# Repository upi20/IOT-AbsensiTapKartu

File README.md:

# Absensi RFID Terintegrasi

Alat absensi **tap kartu RFID** berbasis ESP32 yang **terhubung langsung ke website**. Kartu ditempel, alat mengirim nomornya ke server lewat WiFi (HTTP/HTTPS), dan hasilnya (MASUK / PULANG / tidak terdaftar) tampil di layar sentuh 3.5", LED RGB, dan bunyi buzzer. Semua data kehadiran tersimpan di website, bukan di alat.

*Open-source RFID attendance terminal (ESP32 + RC522 + 3.5" touch LCD) that talks to any web app through a small HTTP API. Includes firmware, a Laravel reference server, integration examples, perfboard/PCB layouts and a 3D-printed case. Documentation is in Indonesian.*

Repositori ini berisi **semua yang dibutuhkan dari nol sampai alat jadi**: daftar komponen, kabel prototipe, firmware, server + panel admin, contoh integrasi ke aplikasi lain, tata letak PCB, dan casing cetak 3D.

---

## Daftar isi

- [Fitur](#fitur)
- [Status proyek](#status-proyek-baca-dulu)
- [Cara kerja](#cara-kerja)
- [Peta tahapan](#peta-tahapan)
- [Tahap 0 — Siapkan komponen, alat, dan software](#tahap-0--siapkan-komponen-alat-dan-software)
- [Tahap 1 — Prototipe dengan kabel jumper](#tahap-1--prototipe-dengan-kabel-jumper)
- [Tahap 2 — Firmware](#tahap-2--firmware)
- [Tahap 3 — Backend (website)](#tahap-3--backend-website)
- [Tahap 4 — PCB](#tahap-4--pcb)
- [Tahap 5 — Casing cetak 3D](#tahap-5--casing-cetak-3d)
- [Pemecahan masalah](#pemecahan-masalah)
- [Struktur folder](#struktur-folder)
- [Untuk kontributor](#untuk-kontributor)
- [Lisensi](#lisensi)

Dokumen lain: [Panduan pengguna untuk klien](doc/panduan-pengguna.md) · [Panduan integrasi aplikasi](doc/integrasi-aplikasi.md) · [Riwayat perubahan](CHANGELOG.md)

---

## Fitur

**Alat (firmware ESP32)**
- Tap kartu MIFARE 13,56 MHz (RC522), hasil tampil dalam ± 0,4–0,6 detik di jaringan normal.
- Semua pengaturan lewat **layar sentuh**: pilih WiFi, isi password, Base URL server, dan API key. Tidak perlu mengubah kode untuk tiap lokasi.
- **Antrean offline** 200 tap: kalau server tidak bisa dihubungi, tap disimpan dan dikirim ulang otomatis (tanpa catatan ganda berkat `tap_id`).
- Foto pemilik kartu (JPEG kecil), pesan dari server, jam tersinkron.
- **Screensaver pengumuman** (judul, isi, ikon) yang diambil dari website.
- **Layar meredup** saat alat diam; kartu tetap terbaca.
- Menu Pengaturan ber-PIN, kalibrasi layar, tes buzzer & LED, cek kabel RFID, reset pabrik (tekan EN 3 kali).
- Heartbeat tiap menit, sehingga website tahu alat mana yang aktif.
- Tahan menyala lama: **watchdog** (restart sendiri kalau program macet) dan **restart harian terjadwal** saat sepi (jamnya diatur per alat dari website, bawaan 03:00).
- **Mode absen**: otomatis (server menentukan datang/pulang) atau **pilih DATANG / PULANG** lewat dua tombol di layar utama (endpoint `/check-in` & `/check-out`), diatur dari menu alat atau dari website.
- Mudah dirawat dari jauh: **kode error di layar** (contoh `E11` = password WiFi salah), laporan kesehatan dan **ringkasan crash** ke website, dan **update firmware jarak jauh (OTA)** yang kembali sendiri ke versi lama kalau firmware baru gagal.

**Website**
- **API sederhana** (`/ping`, `/tap`, `/heartbeat`, opsional `/announcements`) yang bisa diterapkan di aplikasi apa saja: lihat [doc/spesifikasi-api.md](doc/spesifikasi-api.md).
- **Server acuan Laravel** dengan panel admin: anggota & kartu, kehadiran, kartu belum terdaftar, rekap + CSV, daftar alat (PIN per alat), pengumuman, pengaturan (API key, judul, layar redup).
- **Contoh integrasi** PHP dan Node.js tanpa framework, skrip pemeriksa server, dan koleksi Postman lengkap.

---

## Status proyek (baca dulu)

Supaya tidak ada yang tersesat: bagian di bawah ini dibedakan antara yang **sudah diuji di alat sungguhan** dan yang **baru berupa desain**.

| Bagian | Status |
|---|---|
| Prototipe kabel jumper di expansion board | ✅ Dirakit dan berjalan |
| Firmware v1.3.0 | ✅ Berjalan di alat prototipe (tap, antrean, pengumuman, layar redup) |
| Firmware v1.4.0 (watchdog, restart harian, identitas baru) | ✅ Berjalan di alat (boot, tap, heartbeat, watchdog aktif); ⚠️ restart harian **belum diuji** |
| Firmware v1.5.0 (kode error, ringkasan crash, update jarak jauh) | ✅ Update jarak jauh diuji di alat (unduh ± 15 detik, rollback saat restart di masa percobaan juga terbukti); ⚠️ tiap kode error belum diuji satu per satu |
| Server Laravel + panel admin | ✅ Dipakai di server percobaan; 145 tes otomatis lulus |
| Contoh integrasi PHP/Node + Postman | ✅ Lolos skrip pemeriksa dan 114 pemeriksaan Postman |
| Firmware v1.6.0–1.9.1 (mode absen DATANG/PULANG, menu Update firmware, buzzer langsung ke D17) | ✅ Dikirim ke alat lewat update jarak jauh: otomatis 1.5.0 → 1.6.0 → 1.7.0, manual 1.7.0 → 1.8.0 → 1.9.0 → 1.9.1. ⚠️ Mode Pilih Datang/Pulang **belum diuji dengan tap sungguhan** |
| PCB dot matrix (papan bolong 1 sisi 30 × 50) | ✅ Alat pertama dirakit dengan tata letak ini dan berjalan (layar, sentuh, RFID, WiFi, tap, buzzer). ⚠️ Kabel LED (tahap 16) belum diuji; casing belum disesuaikan |
| PCB cetak (KiCad) | ⚠️ Desain lolos DRC, **belum dipesan dan belum diuji** |
| Casing cetak 3D | ⚠️ Desain lolos cek tabrakan otomatis, **belum dicetak** |

Kalau Anda merakit bagian yang bertanda ⚠️, lakukan cek cetak kertas 1:1 yang dijelaskan di tahap itu, dan laporkan hasilnya lewat *Issues*.

---

## Cara kerja

```mermaid
flowchart LR
  K[Kartu RFID] -->|tap| A["Alat<br/>ESP32 + RC522 + LCD"]
  A -->|"POST /tap (WiFi, HTTPS)"| W["Website<br/>(server acuan Laravel<br/>atau aplikasi Anda)"]
  W -->|"status: MASUK / PULANG / ..."| A
  A -.->|heartbeat tiap 1 menit| W
  W -.->|pengaturan & pengumuman| A
  W --> P[Panel admin / laporan]
```

1. Kartu ditempel. Alat membaca UID kartu dan mengubahnya menjadi **nomor 10 digit**.
2. Alat mengirim `POST {Base URL}/tap` dengan header `X-API-Key` dan `X-Device-ID`.
3. Website memutuskan statusnya (`check_in`, `check_out`, `duplicate`, `unknown`, `rejected`) dan membalas nama, pesan, dan (opsional) URL foto.
4. Alat menampilkan hasil, berbunyi, dan menyalakan LED sesuai status.

Website juga bisa mengirim **pengaturan jarak jauh** (PIN menu, judul layar, layar redup) dan **pengumuman** ke alat. Kontrak lengkapnya ada di [doc/spesifikasi-api.md](doc/spesifikasi-api.md).

---

## Peta tahapan

| Tahap | Hasil | Dokumen utama |
|---|---|---|
| 0. Persiapan | Komponen, alat, software siap | bagian di bawah |
| 1. Prototipe | Rangkaian kabel jumper berjalan | [doc/skema-lengkap.md](doc/skema-lengkap.md), [doc/rakit-lengkap.html](doc/rakit-lengkap.html) |
| 2. Firmware | Alat membaca kartu dan tampil di layar | [firmware/](firmware/) |
| 3. Backend | Website menerima tap, panel admin | [api/README.md](api/README.md), [doc/integrasi-aplikasi.md](doc/integrasi-aplikasi.md), [doc/spesifikasi-api.md](doc/spesifikasi-api.md), [contoh-integrasi/](contoh-integrasi/README.md) |
| 4. PCB | Rangkaian rapi tanpa kabel jumper | [doc/rakit-dotmatrix.html](doc/rakit-dotmatrix.html), [doc/pcb-papan-induk.md](doc/pcb-papan-induk.md) |
| 5. Casing | Alat jadi, siap dipasang di dinding | [doc/casing.md](doc/casing.md) |

> **File `.html`** di folder `doc/` adalah panduan interaktif. GitHub hanya menampilkan kodenya, jadi **unduh repositori lalu buka file itu di browser** (dobel klik).

---

## Tahap 0 — Siapkan komponen, alat, dan software

### Komponen (1 unit)

| Komponen | Keterangan | Catatan |
|---|---|---|
| ESP32 DOIT DevKit V1 **30 pin** | Chip USB CH340, jarak dua deret pin 25,4 mm | Varian 38 pin **tidak** cocok dengan PCB dan casing |
| LCD 3.5" SPI **ILI9488** + touch **XPT2046** | 480 × 320, 14 pin di satu sisi pendek, PCB 98 × 56,34 mm (kompatibel LCDWIKI MSP3520) | Jumper **J1** di belakang LCD harus disolder (lihat Tahap 1) |
| RFID **RC522** | Modul standar 60 × 40 mm, 8 pin, 3,3 V | Header pin lurus |
| LED RGB 5 mm **common cathode** | 4 kaki, kaki terpanjang = katoda (−) | Bukan *common anode* |
| Buzzer **aktif** 3–5 V | 2 kaki, berbunyi sendiri bila diberi tegangan | Bukan buzzer pasif |
| Kartu / gantungan kunci MIFARE 13,56 MHz | Biasanya satu paket dengan RC522 | |
| Kabel USB data + adaptor 5 V | Untuk daya alat | |

**Untuk prototipe (Tahap 1):** expansion board ESP32 30 pin (header G-V-S per pin) dan ± 30 kabel jumper female-female.
**Untuk versi rapi (Tahap 4):** papan dot matrix atau PCB cetak beserta komponen kecilnya (resistor, transistor, dioda, kapasitor, header female). Daftarnya ada di tahap itu.

### Alat

Solder + timah, tang potong, multimeter (mode bunyi dan volt DC), obeng kecil. Untuk Tahap 4: cutter, bor 3 mm, lem. Untuk Tahap 5: baut M3 dan spacer.

### Software

| Software | Untuk | Versi yang dipakai di proyek ini |
|---|---|---|
| [Arduino IDE 2](https://www.arduino.cc/en/software) (atau `arduino-cli`) | Firmware | IDE 2.3.10 / arduino-cli 1.5.1 |
| Paket board **esp32 by Espressif Systems** | Firmware | 3.3.12 |
| PHP 8.3 + Composer + PostgreSQL | Server acuan (Tahap 3) | PHP 8.3, Laravel 13 |
| KiCad 10 (opsional) | Membuka / mengubah PCB cetak | 10.0.6 |
| OpenSCAD versi *snapshot* (opsional) | Membuka / mengubah casing | 2026.09.30 |
| Python 3 + PyMuPDF (opsional) | Membuat ulang templat dot matrix | |

---

## Tahap 1 — Prototipe dengan kabel jumper

Tujuannya membuktikan semua komponen berfungsi sebelum dibuat rapi. **Cabut USB setiap kali memasang atau memindah kabel.**

### 1.1 Aturan daya (penting)

- **Semua komponen memakai 3,3 V.** Jangan ada kabel ke pin 5V.
- Di expansion board, jumper **JUMP** harus di posisi **3.3V** (mengatur semua pin V).
- Pakai satu kabel USB saja, ke port **ESP32** (bukan port expansion).
- ESP32 hanya bisa tersambung ke WiFi **2,4 GHz**.

### 1.2 Solder jumper J1 di LCD

Menurut skema resmi modul LCD: kalau VCC diberi **3,3 V**, jumper **J1 harus disambung** (dijembatani timah). Kalau VCC 5 V, J1 dibiarkan terbuka. Rangkaian ini memakai 3,3 V, jadi:

1. Cari bantalan bertanda **J1** di belakang LCD (dekat regulator U1).
2. Sambungkan kedua bantalannya dengan sedikit timah.
3. Setelah J1 disambung, **VCC LCD tidak boleh lagi diberi 5 V**: chip layar bisa rusak.

### 1.3 Pasang kabel

Ikuti [doc/skema-lengkap.md](doc/skema-lengkap.md) (versi interaktif: [doc/rakit-lengkap.html](doc/rakit-lengkap.html)). Ringkasan pin:

| Bagian | Pin modul → GPIO ESP32 |
|---|---|
| LCD | VCC → 3V3, GND → GND, CS → 5, RESET → 4, DC → **16**, SDI → 23, SCK → 18, **LED → 2**, SDO tidak disambung |
| Touch | T_CLK → 22, T_CS → 15, T_DIN → 21, T_DO → 19, T_IRQ tidak disambung |
| RC522 | SDA → 33, SCK → 14, MOSI → 13, MISO → 35, RST → 32, 3.3V → 3V3, GND → GND, IRQ tidak disambung |
| Buzzer aktif | + → 17, − → GND |
| LED RGB | R → 25, G → 26, B → 27, kaki terpanjang (K) → GND |
| *atau* RTC DS3231 (pengganti LED) | SDA → 25, SCL → 26, VCC → 3V3, GND → GND |

Catatan:
- **DC jangan di GPIO2.** Pin LED LCD (lampu latar) memang di GPIO2; firmware memakainya untuk meredupkan layar. Kalau LED LCD disambung ke 3V3, layar menyala terus tanpa fitur redup.
- Pin **GPIO12 jangan dipakai** (pin boot yang membuat ESP32 gagal menyala).
- Resistor 220–330 Ω di tiap kaki warna LED RGB disarankan. Untuk prototipe boleh tanpa resistor karena firmware membatasi arus pin.
- **RTC DS3231 (opsional, firmware 1.10.0+)** menyimpan jam selama listrik mati, sehingga tap saat alat menyala tanpa internet tetap tercatat dengan jam aslinya. RTC memakai pin LED RGB (25, 26), jadi pilih salah satu: LED **atau** RTC. Firmware mendeteksinya sendiri saat menyala. Pakai modul **DS3231** (mis. ZS-042, 3,3 V), bukan DS1307 (butuh 5 V). Di papan dot matrix: kabel header LED dipakai ulang (R = SDA, G = SCL, K = GND), dan kaki R3 yang tersambung ke D27 dipindah ke 3V3 sehingga B = VCC. Jam internet tetap diutamakan; RTC disetel ulang darinya.

### 1.4 Tes per bagian

Sebelum menjalankan tes, siapkan software di [Tahap 2.1](#21-pasang-software). Sketsa tes ada di [firmware/tes/](firmware/tes/):

| Urutan | Sketsa | Yang dites | Hasil yang benar |
|---|---|---|---|
| 1 | `tes_touch` | Layar + layar sentuh | Muncul kalibrasi 3 titik, lalu mode menggambar: titik muncul tepat di bawah jari/stylus |
| 2 | `tes_miso` | Kabel MOSI dan MISO RC522 tidak bersentuhan | Monitor serial menulis `AMAN` terus-menerus |
| 3 | `tes_rfid` | RC522 menjawab | Baris pertama (susunan kabel yang direncanakan) diakhiri `<== RC522 MENJAWAB` |

Buzzer dan LED dites dari firmware utama (menu **Tes buzzer & LED**), setelah Tahap 2.

---

## Tahap 2 — Firmware

Kode ada di [firmware/absensi/](firmware/absensi/). Bahasa komentar: Indonesia.

### 2.1 Pasang software

1. Pasang **Arduino IDE 2**.
2. **Tools → Board → Boards Manager**, cari `esp32`, pasang **esp32 by Espressif Systems** (dipakai: 3.3.12). Kalau tidak muncul, tambahkan URL `https://espressif.github.io/arduino-esp32/package_esp32_index.json` di **Settings → Additional boards manager URLs**.
3. **Tools → Manage Libraries**, pasang:

   | Library | Versi dipakai | Untuk |
   |---|---|---|
   | TFT_eSPI (Bodmer) | 2.5.43 | Layar |
   | RFID_MFRC522v2 | 2.0.6 | RC522 |
   | ArduinoJson (Benoit Blanchon) | 7.4.3 | JSON |
   | TJpg_Decoder (Bodmer) | 1.1.0 | Foto |
   | XPT2046_Touchscreen (Paul Stoffregen) | 1.4 | Hanya untuk sketsa `tes_touch` |

   Pengaturan pin layar ada di `tft_setup.h` di folder sketsa dan dibaca otomatis oleh TFT_eSPI. **File library tidak perlu diubah.**
4. **Mac Apple Silicon:** pasang Rosetta 2 (alat `ctags` di paket Arduino masih x86):
   ```bash
   softwareupdate --install-rosetta --agree-to-license
   ```
5. **Windows:** pasang driver **CH340** kalau port COM tidak muncul.

### 2.2 Atur ID alat

Buka [firmware/absensi/config.h](firmware/absensi/config.h), ubah `ID_ALAT` (bawaan `"ABS-001"`). **Setiap alat harus punya ID berbeda**; ID ini dikirim sebagai `X-Device-ID` dan tidak terhapus saat reset pabrik. Isi `""` supaya dibuat otomatis dari alamat MAC (contoh `ABS-79438C`).

Sejak v1.5.0, ID yang dipakai juga disimpan di memori alat. Upload lewat USB memakai `ID_ALAT` di `config.h`. Update jarak jauh (2.7) tidak memakai `ID_ALAT`, tapi ID yang tersimpan di alat, jadi satu file firmware aman dikirim ke semua alat.

Pengaturan lain di file yang sama (biasanya tidak perlu diubah): PIN bawaan `2026`, interval heartbeat 60 detik, batas antrean 200, batas waktu tap 3 detik, layar redup 60 detik ke 20 %.

### 2.3 Upload

**Lewat Arduino IDE (semua sistem operasi):**
1. Buka `firmware/absensi/absensi.ino`.
2. Board: **ESP32 Dev Module** (bukan "DOIT ESP32 DEVKIT V1", karena yang itu tidak punya menu partisi).
3. **Partition Scheme: Minimal SPIFFS (1.9MB APP with OTA/128KB SPIFFS)**. Wajib: firmware ± 1,35 MB tidak muat di partisi bawaan, dan skema ini punya 2 slot untuk update jarak jauh.
4. Upload Speed: **460800** (Mac/Linux). Kalau upload gagal atau di Windows, pakai **115200**.
5. Pilih port, klik Upload. Kalau tertahan di `Connecting....`, tahan tombol **BOOT** sampai persentase muncul.

**Lewat skrip (Mac/Linux, butuh `arduino-cli`):** dari folder `firmware/`:
```bash
./upload.sh -m              # compile + upload firmware utama, lalu buka monitor serial
./upload.sh -c              # compile saja (cek tanpa alat)
./upload.sh -b              # buat file untuk update jarak jauh (lihat 2.7)
./upload.sh tes_rfid -m     # upload sketsa tes
./monitor.sh                # monitor serial 115200 baud, keluar: Ctrl+C
PORT=/dev/ttyUSB0 ./upload.sh    # pilih port sendiri
```
Skrip memakai partisi Minimal SPIFFS dan kecepatan 460800 secara otomatis. `arduino-cli` dicari di `PATH`, lalu di dalam Arduino IDE (macOS). Lokasi lain: `ARDUINO_CLI=/path/arduino-cli ./upload.sh`.

> **Alat dengan firmware ≤ 1.4.0** (partisi lama Huge APP) harus di-upload **sekali lewat USB** ke v1.5.0, karena partisinya berubah. Pengaturan (WiFi, Base URL, API key, PIN, kalibrasi) tetap, tapi antrean tap dan pengumuman yang tersimpan terhapus. Kirim dulu antrean yang tersisa (tunggu sampai Info alat → Antrean = 0). Setelah itu, update berikutnya bisa lewat jarak jauh.

### 2.4 Siapkan server sementara (kalau website belum ada)

Saat pertama menyala, alat meminta **Base URL** dan **API key**. Kalau server Tahap 3 belum siap, jalankan contoh server PHP di laptop (satu WiFi dengan alat):

```bash
cd contoh-integrasi/php
php -S 0.0.0.0:8080 index.php
```

Base URL-nya `http://<IP-laptop>:8080`, API key `ganti-dengan-kunci-anda`. Kartu contoh yang terdaftar: `0218893066` dan `0012345678` (`0055555555` sengaja nonaktif). Kartu Anda sendiri akan tampil "tidak terdaftar" sampai nomornya ditambahkan ke data contoh. Ini cukup untuk membuktikan alat bekerja. Rinciannya: [contoh-integrasi/README.md](contoh-integrasi/README.md).

### 2.5 Pertama kali menyala

Alat baru (atau setelah reset pabrik) menjalankan urutan ini:
1. **Kalibrasi layar sentuh** 3 titik (hanya kalau belum pernah).
2. **Panduan 4 langkah:**
   1. **WiFi**: pilih dari hasil pindai (atau "Ketik manual"), isi password.
   2. **Base URL**: sudah terisi `https://`. Lengkapi, contoh `https://absensi.example.com/api/absensi` atau `http://192.168.1.10:8080`. Tanpa `/` di akhir.
   3. **API key**: sama persis dengan di server.
   4. **Tes koneksi**, lalu **Simpan**.
3. Layar utama tampil. Tempel kartu.

Monitor serial (115200 baud) menampilkan catatan seperti `RFID: RC522 terdeteksi`, `HTTP POST /tap -> 200`, dan `Tap: 245 ms`.

### 2.6 Menu dan fitur alat

| Fitur | Cara |
|---|---|
| Menu Pengaturan | Ikon gir di layar utama, PIN bawaan **2026** (5 kali salah = terkunci 60 detik). Menu tertutup sendiri setelah 60 detik tanpa sentuhan |
| Isi menu | WiFi, Server, Tes koneksi, Info alat, Ganti PIN, Kalibrasi layar, Tes buzzer & LED (alat dengan RTC: Tes buzzer), Tes screensaver, Cek kabel RFID, Mode absen, Update firmware, Reset pabrik |
| Mode absen | Menu **Mode absen**: **Otomatis** (semua tap ke `/tap`, server menentukan datang/pulang) atau **Pilih Datang / Pulang**: layar utama menampilkan tombol **DATANG** dan **PULANG**. Petugas memilih sekali, lalu semua tap dikirim ke `/check-in` atau `/check-out` sampai diganti. Pilihan dikosongkan otomatis saat tanggal berganti; tap sebelum memilih tidak dikirim. Bisa juga diatur per alat dari website (`config.tap_mode`) |
| Kalibrasi ulang layar | Menu **Kalibrasi layar**, atau tekan **EN** lalu tekan **BOOT** saat muncul "Tekan BOOT sekarang" (jeda 1 detik) |
| Reset pabrik | Tekan **EN 3 kali berturut-turut** (masing-masing sebelum alat menyala 5 detik), lalu pilih "Ya, reset"; atau lewat menu. Menghapus WiFi, URL, API key, PIN, judul, kalibrasi, antrean, pengumuman. **ID alat tidak terhapus** |
| Layar redup | Setelah diam 60 detik, layar meredup ke 20 %. Kartu tetap diproses. Sentuhan pertama hanya menyalakan layar. Angka bisa diubah dari website (`dim_after`, `dim_level`) |
| Antrean offline | Server tidak terjangkau → tap disimpan (maks. 200) dan dikirim ulang saat alat diam |
| Restart harian | Sekali sehari pada jam yang diatur per alat di website (bawaan **03:00**, jam alat), hanya saat alat diam. Antrean tap tetap tersimpan. Kosongkan jamnya di website untuk mematikan |
| Watchdog | Kalau program macet lebih dari 60 detik, alat restart sendiri. Alasan restart terakhir terlihat di **Info alat → Restart** dan dikirim ke website |
| Kode error | Masalah tampil di baris bawah layar utama dengan kode, contoh **E11 Password WiFi salah**. Daftar lengkap di 2.8. Kode yang sedang aktif juga ada di **Info alat → Error** |
| Laporan ke website | Tiap menit: sinyal, RAM, status RFID, antrean, kode error, alasan restart, dan ringkasan crash terakhir. Website menandai alat yang perlu diperhatikan |
| Update jarak jauh | Firmware baru diunggah di website, lalu alat memasangnya sendiri saat diam, **atau langsung lewat menu Update firmware** (lihat 2.7) |
| Pengaturan dari website | PIN menu (per alat), jam restart (per alat), judul layar, layar redup, pengumuman, update firmware (per alat) |

### 2.7 Update firmware jarak jauh (OTA)

Dipakai untuk memperbarui alat yang sudah terpasang di lokasi **tanpa kabel USB**: file firmware diunggah ke website, lalu alat mengunduh dan memasangnya sendiri.

**Syarat (cukup dicek sekali):**
- Alat sudah ber-firmware **1.5.0 atau lebih baru**. Alat dengan firmware lama harus di-upload lewat USB dulu (lihat catatan di 2.3), karena partisinya berbeda.
- Website mendukung update firmware. Server acuan Laravel (Tahap 3.A) sudah punya menu **Firmware**. Aplikasi sendiri: lihat [doc/spesifikasi-api.md](doc/spesifikasi-api.md) bagian 6.1.

#### Langkah 1 — Naikkan nomor versi

Buka [firmware/absensi/config.h](firmware/absensi/config.h) dan ubah `VERSI_FIRMWARE`, contoh `"1.5.0"` → `"1.5.1"`.

Wajib: alat **mengabaikan** update yang versinya sama dengan versi yang sedang terpasang, dan website menolak file yang di dalamnya tidak ada nomor versi yang Anda isi.

#### Langkah 2 — Build file `.bin`

File untuk OTA **bukan** hasil upload biasa. ID alat tidak boleh ikut tertanam, supaya satu file bisa dikirim ke semua alat dan tiap alat tetap memakai ID-nya sendiri. Pilih salah satu cara:

**Cara A — skrip (Mac/Linux, disarankan).** Dari folder `firmware/`, tanpa alat tersambung:
```bash
./upload.sh -b
```
Hasilnya di folder `firmware/build/`:

| File | Untuk apa |
|---|---|
| `absensi-1.5.1.bin` | **Diunggah ke website** (Langkah 3) |
| `absensi-1.5.1.elf` | **Simpan baik-baik** (jangan diunggah). Hanya file ini yang bisa menerjemahkan laporan crash dari versi 1.5.1 (lihat 2.8) |
| `absensi/` | File sementara hasil compile, abaikan |

**Cara B — Arduino IDE (semua sistem operasi).**
1. Di `config.h`, hapus `//` di depan baris `// #define OTA_BUILD`, sehingga menjadi `#define OTA_BUILD`.
2. Board dan Partition Scheme sama seperti 2.3 (**ESP32 Dev Module**, **Minimal SPIFFS (1.9MB APP with OTA/128KB SPIFFS)**).
3. Menu **Sketch → Export Compiled Binary**. Tunggu sampai selesai.
4. Buka folder `firmware/absensi/build/esp32.esp32.esp32/`. Yang diunggah ke website adalah **`absensi.ino.bin`**. Jangan pakai `absensi.ino.merged.bin`, `absensi.ino.bootloader.bin`, atau `absensi.ino.partitions.bin`. Simpan juga `absensi.ino.elf`, beri nama sesuai versinya.
5. **Kembalikan `//` di depan `#define OTA_BUILD`.** Kalau lupa, upload lewat USB ke alat baru tidak memakai `ID_ALAT`, tapi ID dari MAC (contoh `ABS-79438C`).

#### Langkah 3 — Unggah dan pilih alat (server acuan)

1. Panel admin → **Firmware** → **Unggah firmware**. Isi **Versi** sama persis dengan `VERSI_FIRMWARE` (contoh `1.5.1`), pilih file `.bin`, lalu klik **Unggah**.
2. Panel admin → **Alat** → di kartu alat yang akan diperbarui, pilih **Update firmware ke: 1.5.1**, lalu simpan. Status alat menjadi **"Menunggu alat mengunduh"**.
3. Untuk semua alat sekaligus, pakai tombol **Terapkan ke semua alat** di halaman Firmware. **Cobakan dulu ke satu alat** sampai statusnya "Sudah terpasang", baru ke semua.

#### Langkah 4 — Tunggu alat memasang sendiri

1. Alat menerima tawaran update lewat heartbeat (paling lama 1 menit).
2. Update baru mulai saat **tidak ada kartu atau sentuhan selama 1 menit**, supaya orang yang sedang absen tidak terganggu.
3. Layar menampilkan **"Memperbarui firmware v1.5.0 → v1.5.1"**, bilah kemajuan, dan **"Jangan cabut listrik alat"**. Unduhan memakan waktu ± 15–60 detik, tergantung internet.
4. Alat mengecek isi file (MD5), menampilkan "Firmware terpasang", lalu restart dengan versi baru.
5. Di halaman Alat, status menjadi **"Sudah terpasang"**, dan riwayat kejadian mencatat `Firmware 1.5.0 -> 1.5.1`.

**Atau pasang sekarang juga (manual, firmware 1.7.0 ke atas):** di alat buka **Pengaturan → Update firmware**. Alat langsung bertanya ke server. Kalau muncul **"Tersedia v…"**, tekan **Pasang sekarang** → **Pasang**. Cara ini tidak menunggu alat diam dan tidak menunggu jeda 30 menit setelah gagal, dan alasan kegagalan tampil di layar. Server hanya menawarkan versi yang **sudah dijadwalkan untuk alat itu** (Langkah 3). Kalau belum dijadwalkan, menu menjawab "Sudah versi terbaru".

Selama update, buzzer diam, LED menyala biru, dan tampilan lain (jam, sinyal) berhenti sebentar: semua kemampuan alat dipakai untuk mengunduh. Itu wajar selama bilah kemajuan bergerak.

#### Kalau ada yang salah

| Yang terjadi | Artinya / yang dilakukan |
|---|---|
| Server sudah menawarkan update tapi alat tidak kunjung memasang | Alat sedang dipakai, menu Pengaturan sedang terbuka, atau percobaan pertama gagal tersambung (alat lalu menunggu 30 menit). Pakai **menu Update firmware** untuk memasang langsung dan melihat alasannya |
| Lama di "Menunggu alat mengunduh" | Alat offline, sedang dipakai terus, atau firmware alat masih < 1.5.0. Cek status Online dan versi firmware alat |
| Layar "Update firmware gagal" | Unduhan putus atau file rusak. Alat tetap memakai versi lama dan **mencoba lagi 30 menit kemudian**. Alasannya terlihat di Info alat → Firmware |
| Riwayat: "Firmware 1.5.1 -> 1.5.0" tanpa status gagal | Listrik padam atau tombol EN ditekan di menit pertama setelah update, jadi alat kembali ke versi lama untuk berjaga-jaga. Bukan salah firmware: alat **mengulang update sendiri** (paling banyak 3 kali) |
| Status "Gagal, kembali ke 1.5.0" | Firmware baru crash, macet (watchdog), atau listrik drop (brownout) sebelum dinyatakan sehat (5 menit, atau 1 menit setelah server tersambung), jadi alat **kembali sendiri ke versi lama**. Versi itu tidak dicoba lagi. Perbaiki kodenya (lihat laporan crash di riwayat kejadian), naikkan versi (1.5.2), lalu unggah ulang |
| Website menolak file | Versi yang diisi tidak ditemukan di dalam file (lupa Langkah 1, atau salah ketik), file bukan `absensi.ino.bin`, atau ukuran lebih dari 1,9 MB |

Jangan cabut listrik selama layar "Memperbarui firmware" dan di menit pertama setelah alat restart. Kalaupun terjadi, alat tidak rusak: saat mengunduh, firmware baru ditulis ke slot cadangan dan baru dipakai setelah selesai dicek; sesudah restart, alat kembali ke versi lama lalu mengulang update.

Catatan keamanan: alat memakai HTTPS tanpa pemeriksaan sertifikat (sama seperti request lain). Orang yang bisa menyadap jaringan alat secara teori bisa mengirim firmware palsu. Karena itu, update hanya dikirim ke alat yang dipilih di website.

### 2.8 Kode error di layar

Konsumen cukup menyebutkan kode yang tampil di baris bawah layar (atau di **Info alat → Error**).

| Kode | Arti | Yang dicek |
|---|---|---|
| E10 | WiFi tidak ditemukan | Router menyala? Nama WiFi benar? WiFi harus **2,4 GHz**. Alat terlalu jauh dari router? |
| E11 | Password WiFi salah | Ganti password di Pengaturan → WiFi (password router mungkin baru diganti) |
| E12 | WiFi gagal tersambung | Router penuh atau menolak perangkat baru (filter MAC). Restart router |
| E13 | WiFi tidak memberi alamat IP | DHCP router mati atau alamat habis. Restart router |
| E20 | Server tidak bisa dihubungi | Internet lokasi putus, atau Base URL salah alamat. Buka website dari HP di WiFi yang sama |
| E21 | API key salah | Samakan API key di alat (Pengaturan → Server) dengan di website |
| E22 | Alat ditolak server | Alat dinonaktifkan / belum diizinkan di website |
| E23 | Alamat API salah | Base URL keliru (harus diakhiri jalur API, tanpa `/` di akhir), atau `http` vs `https` |
| E24 | Server error / sibuk | Masalah di website (HTTP 5xx / 429). Tap tetap disimpan di antrean |
| E25 | Balasan server tidak valid | Base URL mengarah ke halaman biasa, bukan API |
| E26 | Server terlalu lama menjawab | Internet lambat atau server berat |
| E30 | Pembaca RFID tidak terdeteksi | Kabel RC522 longgar. Menu → Cek kabel RFID |
| E31 | Jam belum sinkron | Server tidak mengirim `server_time` dan NTP diblokir jaringan, atau alat menyala tanpa internet dan tidak punya RTC (atau baterai RTC habis) |

**Membaca laporan crash.** Kalau alat pernah crash, halaman Alat di website menampilkan alamat seperti `0x400d4634 0x400880ed` beserta id build. Terjemahkan alamat itu dengan file `.elf` dari versi yang sama:

```bash
~/Library/Arduino15/packages/esp32/tools/esp-x32/*/bin/xtensa-esp32-elf-addr2line -pfiaC \
  -e firmware/build/absensi-1.5.0.elf 0x400d4634 0x400880ed
```
Hasilnya berupa nama fungsi dan baris kode penyebab crash. Linux: ganti `~/Library/Arduino15` dengan `~/.arduino15`.

---

## Tahap 3 — Backend (website)

Pilih salah satu (boleh keduanya):

### 3.A Pakai server acuan Laravel (paling cepat)

Server lengkap dengan panel admin ada di [api/](api/README.md). Ringkasnya:

```bash
cd api
composer install
cp .env.example .env          # isi DB_* (PostgreSQL) dan APP_URL
php artisan key:generate
php artisan migrate           # membuat akun "admin" (tanpa password) dan API key acak
php artisan absensi:admin-password admin
php artisan storage:link
./serve.sh                    # http://127.0.0.1:8133
```

Kebutuhan: PHP ^8.3 (ekstensi pdo_pgsql, mbstring, fileinfo; gd untuk foto), Composer, **PostgreSQL** (SQLite/MySQL tidak didukung). Tidak perlu Node/npm.

Di panel admin (`/admin`):
1. **Pengaturan**: salin **Base URL** (`<APP_URL>/api/absensi`) dan **API key**, isikan di alat.
2. Tempel kartu di alat. Kartu baru muncul di **Kartu belum terdaftar** → klik **Daftarkan** → isi nama → simpan.
3. Tempel lagi: alat menampilkan **MASUK** (tap pertama hari itu). Tap lagi dalam 60 detik = **sudah tercatat**; tap setelahnya = **PULANG**.

Langkah lengkap, opsi, dan perintah artisan: [api/README.md](api/README.md).

### 3.B Integrasikan ke aplikasi Anda sendiri

Alat tidak terikat ke Laravel. Aplikasi apa pun (PHP, Node, Python, Go, ...) bisa memakainya.

1. **Mulai dari [doc/integrasi-aplikasi.md](doc/integrasi-aplikasi.md)**: gambaran besar, **6 fitur wajib** (Kartu belum terdaftar, Rekap, Alat, Firmware, Pengumuman, Pengaturan), data yang perlu disimpan, urutan kerja, dan checklist siap pakai.
2. Kontrak teknis alat ↔ aplikasi: [doc/spesifikasi-api.md](doc/spesifikasi-api.md).
3. Salin pola dari server contoh yang sudah menjalankan keenam fitur: [contoh-integrasi/php/index.php](contoh-integrasi/php/index.php) atau [contoh-integrasi/node/server.js](contoh-integrasi/node/server.js) ([cara pakai](contoh-integrasi/README.md)).
4. Uji aplikasi Anda dengan [contoh-integrasi/tes/cek-server.sh](contoh-integrasi/tes/cek-server.sh) dan koleksi Postman di [contoh-integrasi/postman/](contoh-integrasi/postman/) (bisa otomatis dengan Newman).

### 3.C Online di internet

- Alat mendukung **HTTPS** (sertifikat tidak diverifikasi, jadi tetap gunakan API key yang panjang dan acak).
- Pasang server di VPS (nginx + PHP-FPM) atau jalankan di komputer sendiri dan buka lewat **Cloudflare Tunnel**. Penjelasannya ada di [api/README.md](api/README.md#memasang-di-internet).
- Untuk server publik: `APP_ENV=production`, `APP_DEBUG=false`, dan buat API key baru dari halaman Pengaturan.

---

## Tahap 4 — PCB

Setelah prototipe berjalan, pindahkan rangkaian ke papan supaya rapi dan muat di casing. Ada dua pilihan dengan **posisi soket LCD yang sama**, sehingga casingnya serupa:

| | A. PCB dot matrix (papan bolong) | B. PCB cetak |
|---|---|---|
| Biaya | Paling murah | Biaya cetak + ongkir |
| Cara | Rakit dan sambung kabel sendiri | Pesan ke pabrik, solder komponen |
| Status | Tata letak & panduan selesai, belum dirakit fisik | Desain lolos DRC, belum dipesan |
| Panduan | [doc/rakit-dotmatrix.html](doc/rakit-dotmatrix.html) (LED RGB), [doc/rakit-dotmatrix-rtc.html](doc/rakit-dotmatrix-rtc.html) (modul jam RTC + baterai cadangan, tanpa LED), [doc/rakit-dotmatrix-ups.html](doc/rakit-dotmatrix-ups.html) (versi RTC + pantau baterai di layar) | [doc/pcb-papan-induk.md](doc/pcb-papan-induk.md) |

Pada kedua pilihan, ESP32, LCD, dan RC522 **dicolokkan ke header female** (tidak disolder), sehingga mudah diganti. Pin yang dipakai sama dengan prototipe, jadi **firmware tidak berubah**.

### 4.A PCB dot matrix

1. Bahan per unit: papan dot matrix **1 sisi** 9 × 15 cm berisi **30 × 50 lubang** (label kolom `1a`–`1z`, `2a`–`2d`, baris `001`–`050`), header female 1×15 ×2, 1×14 ×1, 1×8 ×1, header male 1×4 (kabel LED), resistor 220 Ω ×3, elko **220 µF**, keramik **47 nF** ×2, buzzer aktif 12 mm, kabel silikon 24 AWG merah dan hitam, kabel jumper female 4 jalur untuk LED. Papan dipakai utuh; baris 042–050 tidak dipakai.
2. Buka [doc/rakit-dotmatrix.html](doc/rakit-dotmatrix.html) di browser dan ikuti langkahnya. Semua komponen dipasang di **depan** (sisi polos) dan disolder di **belakang** (sisi tembaga); kabel disolder langsung menempel ke kaki, tanpa lubang tembus. Buzzer langsung ke D17 (tanpa transistor), LED dipasang di casing lewat kabel. Papan di halaman itu bisa dibalik depan/belakang, dan setiap kabel punya kode serta posisi lubang yang ditulis **sama dengan label di papan** (`1z-024` = kolom 1z, baris 024).
3. Opsional: cetak templat 1:1 [hardware/dotmatrix/hasil/templat-1-1.pdf](hardware/dotmatrix/hasil/templat-1-1.pdf) (A4 tegak, skala 100 %, garis skala harus tepat 50 mm) sebagai peta di samping papan.

> Tata letak ini memakai papan 30 × 50. LCD lebih lebar dari papan dan menjorok ke kiri dan atas, jadi **casing (Tahap 5) belum cocok** untuk versi dot matrix ini dan akan dirancang ulang.

Semua posisi berasal dari satu file, [hardware/dotmatrix/tata_letak.py](hardware/dotmatrix/tata_letak.py). Kalau diubah, jalankan `python3 hardware/dotmatrix/tata_letak.py` untuk memperbarui panduan HTML, data JSON, dan templat ketiga versi (led, rtc, ups) (PDF dibuat kalau PyMuPDF terpasang; kalau tidak, cetak file SVG-nya dari browser dengan skala 100 %).

### 4.B PCB cetak

Desain KiCad ada di [hardware/pcb/](hardware/pcb/). File siap pesan sudah tersedia di [hardware/pcb/hasil/](hardware/pcb/hasil/) (Gerber `.zip` untuk JLCPCB atau pabrik lain, PDF cetak 1:1, gambar 3D). Langkah memesan, cek cetak kertas 1:1, dan merakit: [doc/pcb-papan-induk.md](doc/pcb-papan-induk.md).

---

## Tahap 5 — Casing cetak 3D

Casing dua bagian (depan + tutup belakang, 105,8 × 113,8 × 41,2 mm) dibuat di OpenSCAD dari ukuran PCB, dengan jendela LCD, area **TEMPEL KARTU**, tabung cahaya LED, lubang USB-C di samping, lubang tombol EN/BOOT, dan gantungan dinding.

1. File cetak: [hardware/casing/hasil/casing-depan.stl](hardware/casing/hasil/casing-depan.stl) dan [hardware/casing/hasil/casing-belakang.stl](hardware/casing/hasil/casing-belakang.stl), untuk **PCB dot matrix** (bawaan). Untuk PCB cetak, ubah `versi = "pcb"` di [hardware/casing/casing.scad](hardware/casing/casing.scad) lalu buat ulang STL.
2. Saran cetak: **PETG**, layer 0,2 mm, infill 20–30 %, sisi luar menempel ke bed, tanpa support.
3. Baut per unit: spacer M3 11 mm F-F ×8, baut M3×25 ×8, M3×5 ×8, M3×30 ×4.

Panduan lengkap (pesan ke jasa cetak, urutan merakit, cara mengubah ukuran): [doc/casing.md](doc/casing.md).

---

## Pemecahan masalah

| Gejala | Penyebab / solusi |
|---|---|
| Layar menampilkan kode `E..` | Lihat tabel [kode error](#28-kode-error-di-layar) |
| `Sketch too big` | Partition Scheme belum **Minimal SPIFFS (1.9MB APP with OTA)** |
| `fork/exec .../ctags: bad CPU type` (Mac) | Rosetta 2 belum terpasang |
| Upload gagal di 921600 baud | Chip CH340: pakai 460800 atau 115200 |
| Tertahan di `Connecting....` | Tahan **BOOT** sampai upload mulai |
| `Failed to communicate with the flash chip` | Ada kabel menahan pin boot: jangan pakai GPIO12, dan GPIO2 hanya untuk LED LCD |
| `Resource busy` (Mac/Linux) | Port dipakai Serial Monitor. Tutup monitor, atau pakai `firmware/upload.sh` (menghentikannya otomatis) |
| Layar putih polos | Kabel CS, RESET, DC, SDI, SCK |
| Layar gelap | Kabel LED LCD ke GPIO2 lepas, atau firmware lama (< 1.3.0) |
| Sentuhan meleset | Kalibrasi ulang layar |
| `RFID: tidak terdeteksi (versi 0x00)` | Ada kabel RC522 tertukar (sering SDA dan SCK) atau lepas. Jalankan `tes_rfid` |
| Versi `0xFF` | RC522 tidak menjawab: cek 3,3 V, GND, dan solderan header RC522 |
| Versi `0xEE` | Kabel MOSI dan MISO bersentuhan. Jalankan `tes_miso` |
| Tes koneksi gagal | Base URL harus diawali `http://` atau `https://`, tanpa `/` di akhir dan tanpa `/ping`. WiFi harus 2,4 GHz. Untuk server di laptop: izinkan port di firewall |
| Kartu "tidak terdaftar" | Daftarkan kartunya di website (Tahap 3) |

Lebih banyak: [doc/skema-lengkap.md](doc/skema-lengkap.md#9-troubleshooting), [api/README.md](api/README.md), [contoh-integrasi/README.md](contoh-integrasi/README.md).

---

## Struktur folder

```
README.md                 ← panduan ini
LICENSE, NOTICE           ← lisensi Apache-2.0
firmware/
  absensi/                ← firmware alat (absensi.ino, config.h, tft_setup.h, ...)
  tes/                    ← sketsa tes: tes_touch, tes_miso, tes_rfid
  upload.sh, monitor.sh   ← compile/upload & monitor serial (Mac/Linux)
api/                      ← server acuan Laravel + panel admin
contoh-integrasi/         ← contoh server PHP & Node, skrip pemeriksa, koleksi Postman
CHANGELOG.md              ← riwayat perubahan firmware, server, dokumentasi
hardware/
  dotmatrix/              ← tata letak PCB dot matrix (tata_letak.py) + templat 1:1
  pcb/                    ← PCB cetak (KiCad 10): buat_pcb.py, rute.py, buat.sh, hasil/
  casing/                 ← casing 3D (OpenSCAD): casing.scad, buat.sh, hasil/
doc/
  integrasi-aplikasi.md   ← panduan integrasi ke aplikasi lain (6 fitur wajib, Postman)
  spesifikasi-api.md      ← kontrak API alat ↔ website
  skema-lengkap.md        ← kabel prototipe (acuan pin)
  rakit-lengkap.html      ← panduan interaktif kabel prototipe
  rakit-dotmatrix.html    ← panduan interaktif PCB dot matrix (papan 1 sisi 30 × 50), versi LED RGB
  rakit-dotmatrix-rtc.html ← sama, versi modul jam RTC DS3231 (tanpa LED)
  rakit-dotmatrix-ups.html ← sama, versi RTC + pantau baterai UPS (D34, VP)
  panduan-pengguna.md     ← panduan pengguna/klien: absen, mode, menu, kode error, update, perawatan
  pcb-papan-induk.md      ← PCB cetak: pesan, cek, rakit
  casing.md               ← casing: cetak, baut, rakit
```

---

## Untuk kontributor

- **Firmware:** `cd firmware && ./upload.sh -c` untuk memastikan kode tetap bisa dikompilasi.
- **Server:** `cd api && php artisan test --compact` (butuh database `absensi_alat_test`), lalu `vendor/bin/pint`.
- **Contoh integrasi:** `contoh-integrasi/tes/cek-server.sh` terhadap contoh PHP dan Node.
- **PCB cetak:** ubah [hardware/pcb/buat_pcb.py](hardware/pcb/buat_pcb.py), jalankan `hardware/pcb/buat.sh` (saat ini skrip memakai lokasi KiCad di macOS dan mengunduh Java + Freerouting untuk Mac Apple Silicon ke `hardware/pcb/alat/`). DRC harus 0 pelanggaran.
- **Casing:** ubah [hardware/casing/casing.scad](hardware/casing/casing.scad), jalankan `hardware/casing/buat.sh` (butuh `openscad` di PATH). Semua cek tabrakan harus `ok`.
- Teks untuk pengguna dan komentar kode memakai **bahasa Indonesia**.
- Kirim laporan hasil rakit (foto, ukuran yang meleset) lewat *Issues*: sangat membantu bagian yang belum diuji fisik.

---

## Lisensi

[Apache License 2.0](LICENSE). Lihat juga [NOTICE](NOTICE) untuk bagian pihak ketiga.

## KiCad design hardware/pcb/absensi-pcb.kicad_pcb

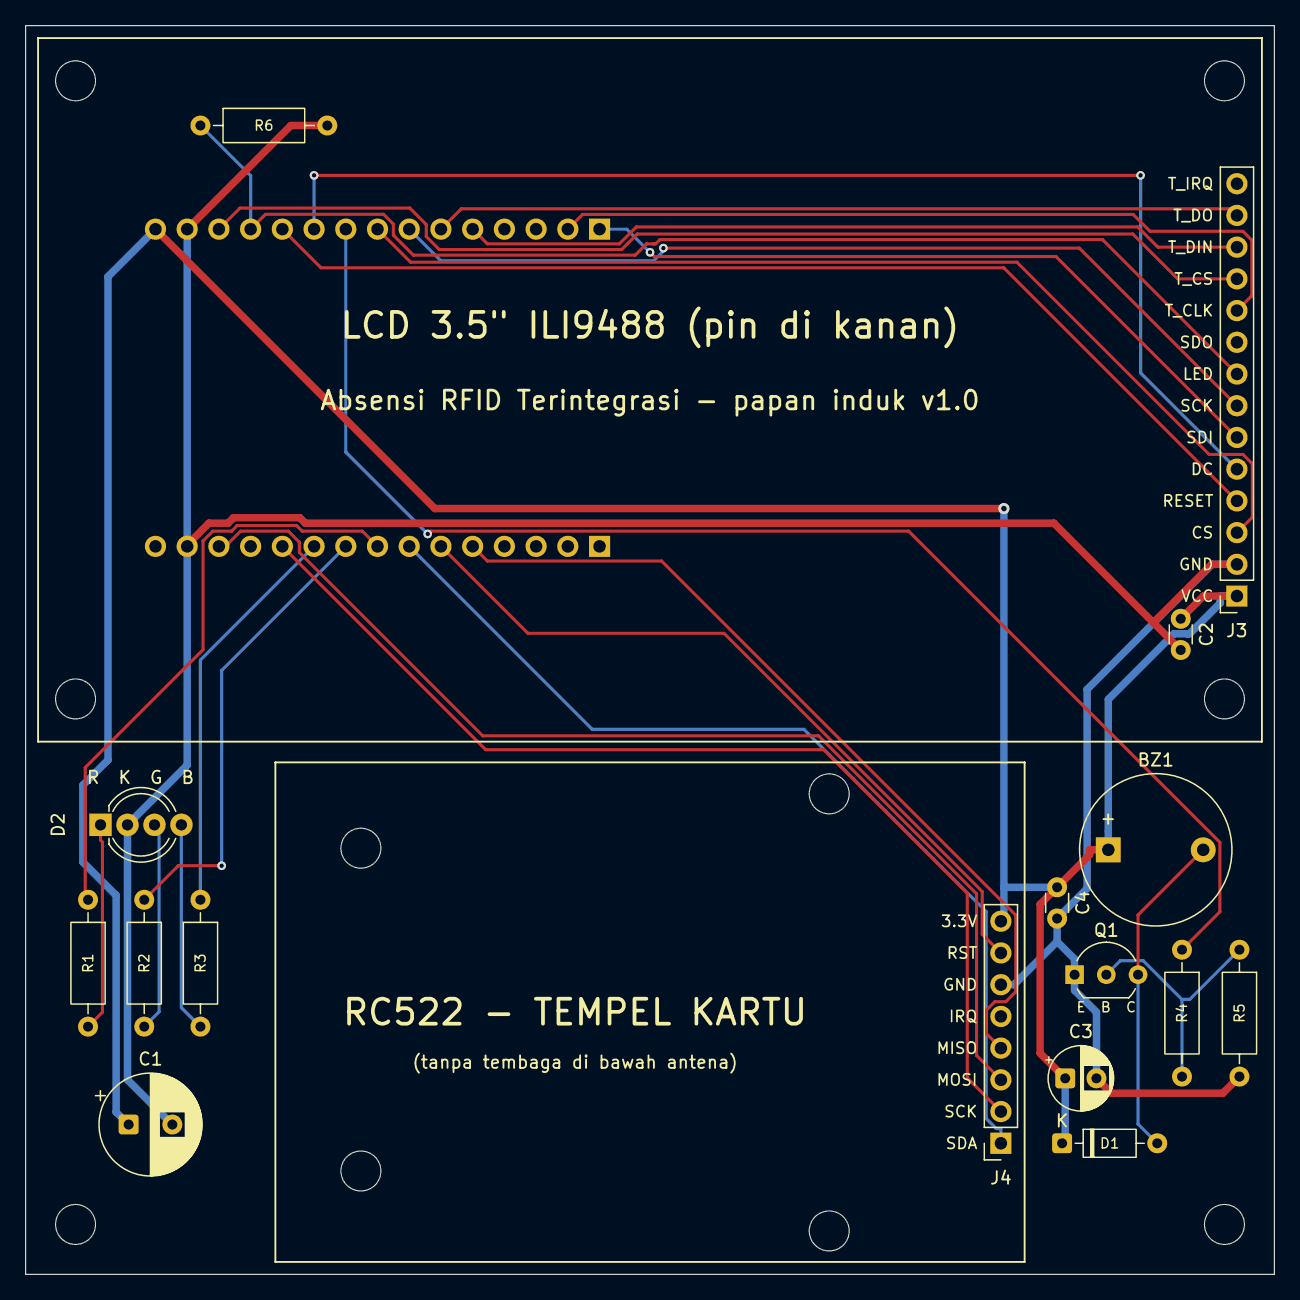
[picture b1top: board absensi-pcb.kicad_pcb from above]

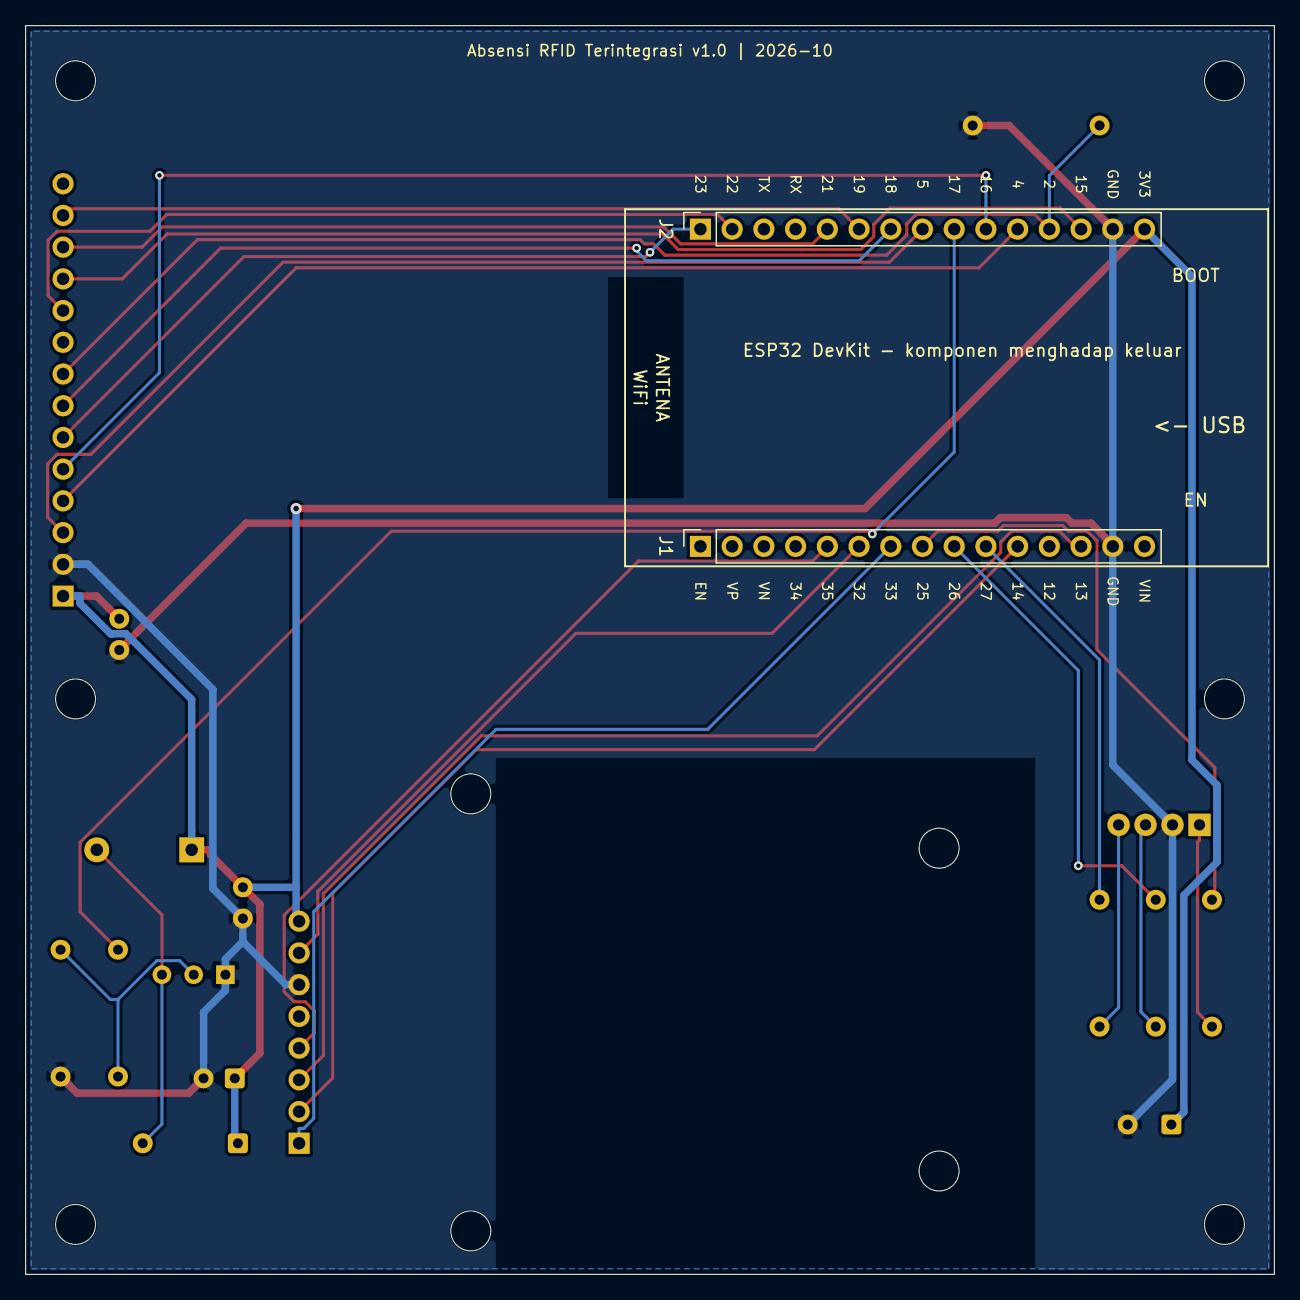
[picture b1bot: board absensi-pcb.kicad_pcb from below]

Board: 2 copper layers, 100.0 x 100.0 mm, 28 parts (2 on the bottom side), 26 nets.

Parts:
BZ1: Buzzer aktif; Buzzer_12x9.5RM7.6
C1: 470uF 10V; CP_Radial_D8.0mm_P3.50mm
C2, C4: 100nF; C_Disc_D3.0mm_W1.6mm_P2.50mm
C3: 10uF; CP_Radial_D5.0mm_P2.50mm
D1: 1N4148; D_DO-35_SOD27_P7.62mm_Horizontal
D2: RGB katoda bersama; LED_D5.0mm-4_RGB_Wide_Pins
H1, H2, H3, H4: M3 LCD; MountingHole_3.2mm_M3
H5, H6, H7, H8: M3 RC522; MountingHole_3.2mm_M3
H9, H10: M3 casing; MountingHole_3.2mm_M3
J1: ESP32 EN..VIN; PinSocket_1x15_P2.54mm_Vertical
J2: ESP32 D23..3V3; PinSocket_1x15_P2.54mm_Vertical
J3: LCD 3.5in; PinSocket_1x14_P2.54mm_Vertical
J4: RC522; PinSocket_1x08_P2.54mm_Vertical
Q1: S8050; TO-92_Inline_Wide
R1, R2, R3: 220; R_Axial_DIN0207_L6.3mm_D2.5mm_P10.16mm_Horizontal
R4: 1k; R_Axial_DIN0207_L6.3mm_D2.5mm_P10.16mm_Horizontal
R5, R6: 10k; R_Axial_DIN0207_L6.3mm_D2.5mm_P10.16mm_Horizontal

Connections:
+3V3: BZ1.1, C1.1, C2.1, C3.1, C4.1, D1.1, J2.15, J3.1, J4.8
BUZ: J2.9, R4.1
BUZ_B: Q1.2, R4.2, R5.1
BUZ_K: BZ1.2, D1.2, Q1.3
GND: C1.2, C2.2, C3.2, C4.2, D2.2, J1.14, J2.14, J3.2, J4.6, Q1.1, R5.2, R6.2
LCD_CS: J2.8, J3.3
LCD_DC: J2.10, J3.5
LCD_LED: J2.12, J3.8, R6.1
LCD_MOSI: J2.1, J3.6
LCD_RST: J2.11, J3.4
LCD_SCK: J2.7, J3.7
LED_B: D2.4, R3.2
LED_B_IO: J1.10, R3.1
LED_G: D2.3, R2.2
LED_G_IO: J1.9, R2.1
LED_R: D2.1, R1.2
LED_R_IO: J1.8, R1.1
RFID_MISO: J1.5, J4.4
RFID_MOSI: J1.13, J4.3
RFID_RST: J1.6, J4.7
RFID_SCK: J1.11, J4.2
RFID_SS: J1.7, J4.1
T_CLK: J2.2, J3.10
T_CS: J2.13, J3.11
T_DIN: J2.5, J3.12
T_OUT: J2.6, J3.13

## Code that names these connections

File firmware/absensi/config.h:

// Pengaturan tetap alat absensi: pin, waktu, versi, dan nilai bawaan pabrik.
// Yang diisi di sini hanya ID alat. WiFi, Base URL, API key, PIN, dan judul diisi lewat layar sentuh
// (disimpan di memori alat, lihat pengaturan.h).
#pragma once

// ---------- ID alat (ubah untuk SETIAP alat sebelum upload) ----------
// Tampil di layar dan dikirim ke server sebagai X-Device-ID. Harus berbeda di tiap alat.
// Kosongkan ("") kalau ingin dibuat otomatis dari MAC, contoh "ABS-79438C".
const char ID_ALAT[] = "ABS-001";

// ---------- Build untuk update jarak jauh / OTA (README 2.7) ----------
// Hanya untuk pengguna Arduino IDE yang membuat file .bin lewat "Export Compiled Binary":
// hapus "//" di depan #define di bawah SEBELUM export, lalu pasang lagi "//" SESUDAHNYA.
// Selama aktif, ID_ALAT di atas tidak dipakai: tiap alat tetap memakai ID yang sudah tersimpan di alat.
// Pengguna ./upload.sh -b tidak perlu mengubah baris ini (skrip mengaktifkannya sendiri).
// #define OTA_BUILD

// ---------- Versi & nilai bawaan pabrik ----------
const char VERSI_FIRMWARE[] = "1.11.4";          // naikkan setiap membuat firmware baru (wajib untuk OTA)
const char VERSI_SPEK[]     = "1";              // versi spesifikasi API (header X-Spec-Version)
const char PIN_BAWAAN[]     = "2026";           // PIN menu Pengaturan sebelum diganti
const char JUDUL_BAWAAN[]   = "Absensi RFID";   // judul layar utama sebelum diganti
const int  OFFSET_BAWAAN    = 7 * 60;           // zona waktu bawaan dalam menit (+07:00 = WIB)
const char NTP_SERVER[]     = "pool.ntp.org";   // cadangan jam kalau server tidak mengirim server_time

// ---------- Waktu (milidetik) ----------
// Batas waktu di bawah ini berlaku untuk SELURUH request: sambung + TLS + tunggu jawaban (+ coba ulang).
const uint32_t HTTP_TIMEOUT_MS       = 8000;    // GET /ping (saat menyala dan "Tes koneksi")
const uint32_t TAP_TIMEOUT_MS        = 3000;    // POST /tap langsung: lewat dari ini tap disimpan di antrean
const uint32_t LATAR_TIMEOUT_MS      = 3000;    // request latar: heartbeat, pengumuman, kirim antrean
const uint32_t HTTP_ULANG_MIN_MS     = 1000;    // sambungan lama gagal: coba ulang hanya kalau sisa waktu masih segini
const uint32_t FOTO_TIMEOUT_MS       = 3000;    // batas unduh foto
const uint32_t DIAM_LATAR_MS         = 5000;    // request latar hanya dikirim kalau tidak ada kartu / sentuhan selama ini
const uint32_t DNS_ULANG_MS          = 600000;  // alamat IP server dicari ulang (DNS) paling cepat tiap 10 menit
const uint32_t HEARTBEAT_INTERVAL_MS = 60000;   // heartbeat tiap 1 menit
const uint32_t ANTREAN_JEDA_MS       = 1000;    // jeda antar kiriman antrean
const uint32_t ANTREAN_ULANG_MS      = 30000;   // antrean gagal terkirim: coba lagi setelah ini
const uint32_t HASIL_TAMPIL_MS       = 4000;    // lama layar hasil tap
const uint32_t MENU_TIMEOUT_MS       = 60000;   // menu Pengaturan ditutup kalau tidak disentuh
const uint32_t KARTU_JEDA_MS         = 3000;    // kartu yang sama diabaikan selama ini
const uint32_t WIFI_BOOT_TIMEOUT_MS  = 15000;   // batas tunggu WiFi saat menyala
const uint32_t WIFI_TES_TIMEOUT_MS   = 15000;   // batas tunggu WiFi saat "Tes koneksi"
const uint32_t PIN_KUNCI_MS          = 60000;   // keypad dikunci setelah PIN salah berkali-kali
const int      PIN_SALAH_MAKS        = 5;       // berapa kali PIN boleh salah
const uint32_t RESET_TANYA_MS        = 15000;   // layar "Reset pabrik?" batal sendiri
const uint32_t PENGUMUMAN_CEK_MS     = 600000;  // pengumuman diambil ulang paling lambat tiap 10 menit
const uint32_t PENGUMUMAN_ULANG_MS   = 60000;   // gagal karena jaringan: coba lagi setelah ini (jeda dilipatgandakan
                                                // tiap gagal lagi, paling lama PENGUMUMAN_CEK_MS)
const uint32_t BOOT_AMAN_MS          = 5000;    // alat menyala lebih lama dari ini = bukan tekan EN beruntun
const int      BOOT_RESET_KALI       = 3;       // tekan EN sebanyak ini dalam 5 detik = tawaran reset pabrik

// ---------- Batas data ----------
const int    PIN_MIN_ANGKA  = 4;                // PIN menu Pengaturan: 4 sampai 8 angka
const int    PIN_MAKS_ANGKA = 8;
const int    JUDUL_UTAMA_MAKS = 30;             // judul layar utama (config.title) paling banyak 30 huruf
const int    ANTREAN_MAKS   = 200;              // tap yang disimpan saat server tidak bisa dihubungi
const size_t FOTO_MAKS_BYTE = 30 * 1024;        // foto paling besar 30 KB
const int    FOTO_MAKS_PX   = 160;              // foto paling besar 160 x 160 piksel

// ---------- Pengumuman / screensaver (doc/spesifikasi-api.md bagian 8) ----------
const int PENGUMUMAN_MAKS   = 10;               // pengumuman paling banyak, sisanya diabaikan
const int JUDUL_MAKS_HURUF  = 40;               // judul lebih panjang dipotong
const int ISI_MAKS_HURUF    = 160;              // deskripsi lebih panjang dipotong
const int INTERVAL_BAWAAN   = 3;                // detik tiap pengumuman tampil (boleh 2-60)
const int DIAM_BAWAAN       = 30;               // screensaver muncul setelah diam sekian detik (boleh 5-600)

// ---------- Lampu layar (doc/spesifikasi-api.md bagian 6, config.dim_after / dim_level) ----------
const int REDUP_DETIK_BAWAAN  = 60;             // layar meredup setelah diam sekian detik (0 = tidak pernah, boleh 10-3600)
const int REDUP_PERSEN_BAWAAN = 20;             // kecerahan saat redup dalam persen (0 = mati, boleh 0-100)

// ---------- Perawatan (perawatan.h) ----------
const uint32_t WATCHDOG_MS          = 60000;    // program macet selama ini -> restart otomatis
const char     RESTART_BAWAAN[]     = "03:00";  // restart harian (jam alat); "" = tidak restart otomatis.
                                                // Diganti per alat lewat config.restart_at dari server
const int      RESTART_JENDELA_MENIT = 30;      // restart boleh terjadi dalam 30 menit sejak jadwal (menunggu alat diam)
const uint32_t RESTART_DIAM_MS      = 120000;   // restart hanya kalau tidak ada kartu / sentuhan selama 2 menit
const uint32_t RESTART_MIN_NYALA_S  = 3600;     // dan alat sudah menyala minimal 1 jam

// ---------- Update firmware jarak jauh / OTA (ota.h) ----------
const uint32_t OTA_DIAM_MS          = 60000;    // update hanya kalau tidak ada kartu / sentuhan selama 1 menit
const uint32_t OTA_ULANG_MS         = 1800000;  // unduh gagal: coba lagi setelah 30 menit
const uint32_t OTA_DATA_TIMEOUT_MS  = 20000;    // unduhan dianggap putus kalau tidak ada data selama ini
const int      OTA_ULANG_MAKS       = 3;        // firmware baru terputus listrik / EN sebelum sehat: dicoba ulang
                                                // sampai 3 kali, baru dianggap gagal
const uint32_t OTA_SEHAT_S          = 300;      // firmware baru dianggap sehat setelah menyala 5 menit tanpa
                                                // crash (atau lebih cepat: 1 menit + server tersambung).
                                                // Kalau crash sebelum itu, alat kembali ke firmware lama.

// ---------- Kode error (galat.h) ----------
const uint32_t WIFI_DHCP_MS         = 10000;    // WiFi tersambung tapi belum dapat alamat IP selama ini -> E13
const uint32_t JAM_TUNGGU_S         = 120;      // jam belum sinkron setelah menyala selama ini -> E31
const uint32_t JADWAL_KEMBALI_MS    = 180000;   // mode pilih + jadwal: pilihan manual yang beda dari jadwal kembali setelah 3 menit

// ---------- Baterai UPS (baterai.h) ----------
const int   BATERAI_LEMAH_MV  = 3400;           // listrik padam dan baterai di bawah ini = peringatan merah
const float BATERAI_KALIBRASI = 1.00;           // tegangan di Info alat beda dengan multimeter? isi multimeter
                                                // dibagi angka di layar, contoh 4,05 / 3,98 = 1.018

// ---------- Lain-lain ----------
const bool BUZZER_AKTIF = true;                 // false = alat tidak berbunyi

// ---------- Pin (sesuai kabel; layar ada di tft_setup.h) ----------
const int PIN_TOMBOL_BOOT = 0;

// Touch XPT2046, jalur sendiri (bit-bang)
const int T_CLK = 22, T_DIN = 21, T_OUT = 19, T_CS = 15;

// RFID RC522, SPI kedua (HSPI)
const int RFID_SCK = 14, RFID_MOSI = 13, RFID_MISO = 35, RFID_SS = 33, RFID_RST = 32;

// Buzzer aktif (HIGH = bunyi) dan LED RGB katoda bersama
const int PIN_BUZZER = 17;
const int PIN_LED_R = 25, PIN_LED_G = 26, PIN_LED_B = 27;

// RTC DS3231 (pengganti LED RGB, di kabel header yang sama): R = SDA, G = SCL, B = VCC 3,3 V. Lihat rtc.h.
// Terdeteksi otomatis: kalau RTC terpasang LED tidak dipakai, kalau tidak ada RTC LED bekerja seperti biasa.
const int RTC_SDA = PIN_LED_R, RTC_SCL = PIN_LED_G;

// Lampu latar LCD (pin LED di LCD), PWM untuk meredup. Pin lain layar ada di tft_setup.h.
const int PIN_LAMPU_LCD = 2;

// Baterai UPS (opsional, baterai.h): titik tengah pembagi 10k + 10k. Kedua pin hanya-input (ADC1).
const int PIN_BATERAI = 34;   // D34: dari + baterai
const int PIN_LISTRIK = 36;   // VP:  dari 5V+ charger (listrik ada / padam)
